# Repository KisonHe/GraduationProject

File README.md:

# ESP32 & RoboMaster motors
水毕设，3508+ESP_Dash，ESP32控制

## LVGL Note
注意检查style的生命周期，要与被赋予style的对象共存亡

```bash
node ./node_modules/lv_font_conv/lv_font_conv.js --font ~/Downloads/NotoSansMonoCJKsc-Regular.otf --symbol "123456abcdef我是中国人" --lcd --size 16 --bpp 4 --format bin -o data/customfont.bin
./node_modules/lv_img_conv/lv_img_conv.js ~/Downloads/gyro-200.png -f -c CF_TRUE_COLOR_ALPHA -t bin --binary-format 565 -o gyro.bin
```

获取Fonts `https://github.com/googlefonts/noto-cjk`

[Download](https://github.com/googlefonts/noto-cjk/raw/main/Sans/Mono/NotoSansMonoCJKsc-Regular.otf)

有空的时候记得修改 `https://github.com/KisonHe/TFT_eSPI_Assi` ，改成支持lv_font_conv

Get Offline Tool
```bash
npm i lv_font_conv
npm i lv_img_conv
```

## ESP32 Note
根据 https://github.com/espressif/arduino-esp32/issues/3079#issuecomment-520161166 
nnd,又要改，直接来吧！

## ESP32 - FreeRTOS
在Commit 754485b中，会出现manager或can read太久没有被执行的问题。TODO:目前没有完全理清楚，初步认定是TaskSkip导致的问题
https://docs.espressif.com/projects/esp-idf/en/v4.3.2/esp32/api-guides/freertos-smp.html#round-robin-scheduling

有趣的现象，如果把lvgl的优先级从2改到22,反而不会出现电机疯掉问题了。初步认为wifi task，isr等以及一大堆task彻底抢占了core0,使得剩下的都在core1上，使得taskskip不再出现

一定要搞清楚！目前为了先弄毕业设计先都pin to core 1

排除以上问题，原因是can的接收频率不稳定，如果can rx是tskNO_AFFINITY则会出现接收频率降低问题。注意官方V4的example
```
xTaskCreatePinnedToCore(twai_receive_task, "TWAI_rx", 4096, NULL, RX_TASK_PRIO, NULL, tskNO_AFFINITY);
```
其中RX_TASK_PRIO为9,需要搞清楚为什么

目前在canrx处于tskNO_AFFINITY情况下，即使将lvgl task降到0也会导致canrx频率下降，急需弄清楚

似乎是因为偷懒带来的惨痛教训，从网上抄的CAN初始化没有仔细看，换成CAN_MODE_NORMAL后似乎没问题了。那么，nnd,为什么从2改到22,反而不会出现电机疯掉问题了？

Nope, is it caused by mqtt? Too late now debug tomorrow. Comment out MQTT see if problem still there. If caused by mqtt consider use https://docs.espressif.com/projects/esp-idf/en/latest/esp32/api-reference/protocols/mqtt.html

大概是WiFi Task在环境太糟糕的时候。。。大概会block太久？没验证，查看丢包现象观察猜测

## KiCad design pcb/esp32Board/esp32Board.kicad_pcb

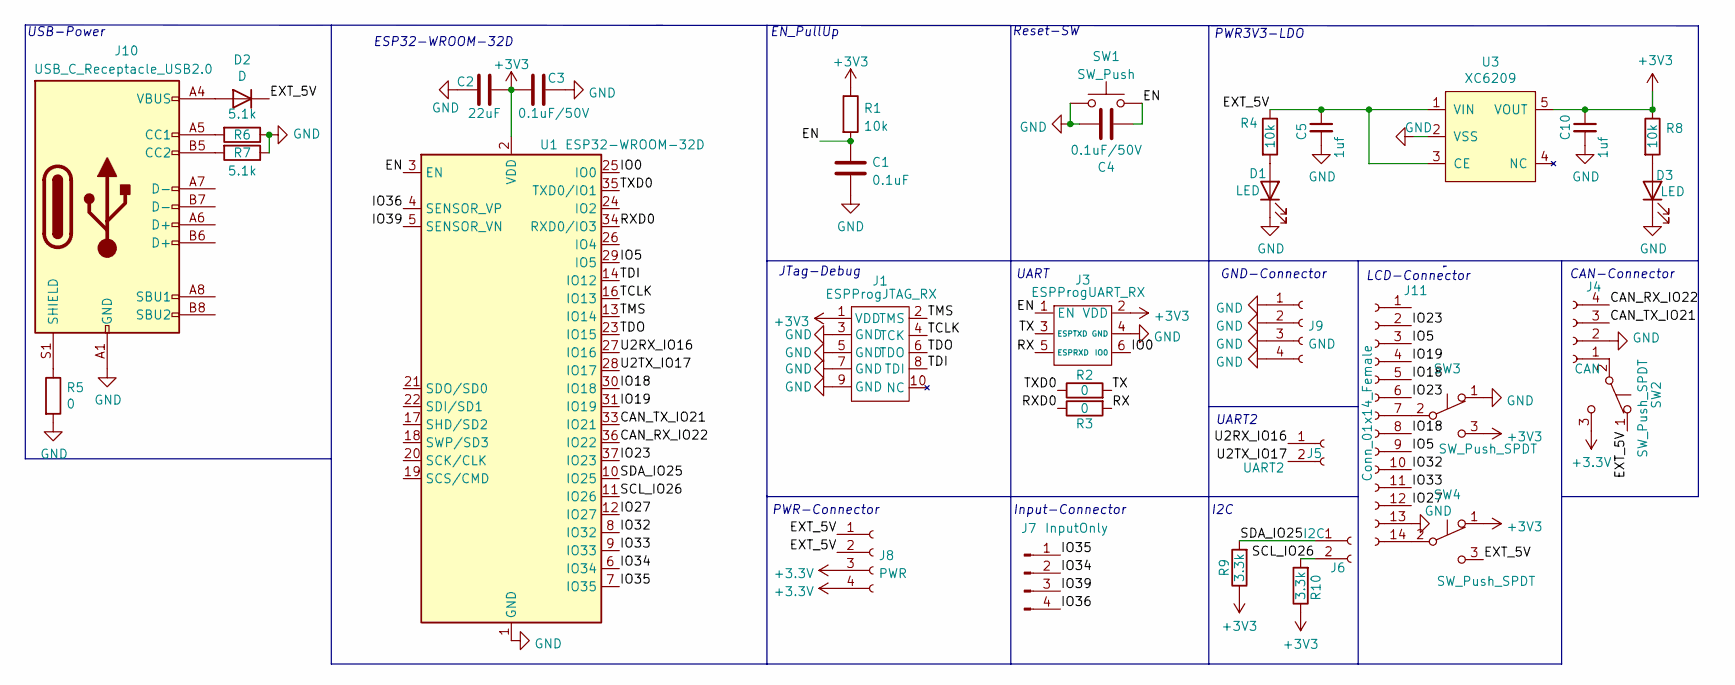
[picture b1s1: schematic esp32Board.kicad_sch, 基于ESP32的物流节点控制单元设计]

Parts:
C1: 0.1uF; C_0603_1608Metric; LCSC C1591
C2: 22uF; C_0603_1608Metric
C3, C4: 0.1uF/50V; C_0603_1608Metric
C5, C10: 1uf; C_0603_1608Metric
D1, D3: LED; LED_0603_1608Metric; LCSC C181863
D2: D; C8678; LCSC C8678
J1: ESPProgJTAG_RX; IDC_1.27mm_10P
J3: ESPProgUART_RX; IDC_1.27mm_6P
J4: CAN; PinHeader_1x04_P2.54mm_Vertical
J5: UART2; PinHeader_1x02_P2.54mm_Vertical
J6: I2C; PinHeader_1x02_P2.54mm_Vertical
J7: InputOnly; PinHeader_1x04_P2.54mm_Vertical
J8: PWR; PinHeader_1x04_P2.54mm_Vertical
J9: GND; PinHeader_1x04_P2.54mm_Vertical
J10: USB_C_Receptacle_USB2.0; USB_C_Receptacle_HRO_TYPE-C-31-M-12; LCSC C165948
J11: Conn_01x14_Female; PinHeader_1x14_P2.54mm_Vertical
R1, R4, R8: 10k; R_0603_1608Metric
R2, R3, R5: 0; R_0603_1608Metric; LCSC C429617
R6, R7: 5.1k; R_0603_1608Metric; LCSC C325524
R9, R10: 3.3k; R_0603_1608Metric; LCSC C429617
SW1: SW_Push; BTN-TS342A4P-WZ-C557592; LCSC C557592
SW2, SW3, SW4: SW_Push_SPDT; 0603JumperP3
U1: ESP32-WROOM-32D; ESP32-WROOM-32
U3: XC6209; SOT-23-5

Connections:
/CAN_RX_IO22: J4.4, U1.36 (IO22)
/CAN_TX_IO21: J4.3, U1.33 (IO21)
/EN: C1.1, C4.1, J3.1 (EN), R1.2, SW1.2, U1.3 (EN)
/EXT_5V: C5.1, D2.1 (K), J8.1, J8.2, R4.1, SW2.1 (A), SW4.3 (C), U3.1 (VIN), U3.3 (CE)
/IO0: J3.6 (IO0), U1.25 (IO0)
/IO5: J11.3, J11.9, U1.29 (IO5)
/IO18: J11.5, J11.8, U1.30 (IO18)
/IO19: J11.4, U1.31 (IO19)
/IO23: J11.2, J11.6, U1.37 (IO23)
/IO27: J11.12, U1.12 (IO27)
/IO32: J11.10, U1.8 (IO32)
/IO33: J11.11, U1.9 (IO33)
/IO34: J7.2, U1.6 (IO34)
/IO35: J7.1, U1.7 (IO35)
/IO36: J7.4, U1.4 (SENSOR_VP)
/IO39: J7.3, U1.5 (SENSOR_VN)
/RX: J3.5 (ESPRXD), R3.2
/RXD0: R3.1, U1.34 (RXD0/IO3)
/SCL_IO26: J6.2, R10.2, U1.11 (IO26)
/SDA_IO25: J6.1, R9.2, U1.10 (IO25)
/TCLK: J1.4 (TCK), U1.16 (IO13)
/TDI: J1.8 (TDI), U1.14 (IO12)
/TDO: J1.6 (TDO), U1.23 (IO15)
/TMS: J1.2 (TMS), U1.13 (IO14)
/TX: J3.3 (ESPTXD), R2.2
/TXD0: R2.1, U1.35 (TXD0/IO1)
/U2RX_IO16: J5.1, U1.27 (IO16)
/U2TX_IO17: J5.2, U1.28 (IO17)
GND: C1.2, C2.1, C3.2, C4.2, C5.2, C10.2, D1.1 (K), D3.1 (K), J1.3 (GND), J1.5 (GND), J1.7 (GND), J1.9 (GND), J3.4 (GND), J4.2, J9.1, J9.2, J9.3, J9.4, J10.A1 (GND), J10.A12 (GND), J10.B1 (GND), J10.B12 (GND), J11.13, R5.2, R6.1, R7.1, SW1.1, SW3.1 (A), U1.1 (GND), U1.15 (GND), U1.38 (GND), U1.39 (GND), U3.2 (VSS)
unnamed: D1.2 (A), R4.2
unnamed: D2.2 (A), J10.A4 (VBUS), J10.A9 (VBUS), J10.B4 (VBUS), J10.B9 (VBUS)
unnamed: D3.2 (A), R8.2
unnamed: J4.1, SW2.2 (B)
unnamed: J10.A5 (CC1), R6.2
unnamed: J10.B5 (CC2), R7.2
unnamed: J10.S1 (SHIELD), R5.1
unnamed: J11.7, SW3.2 (B)
unnamed: J11.14, SW4.2 (B)

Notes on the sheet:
ESP32-WROOM-32D
Input-Connector
LCD-Connector
PWR3V3-LDO
CAN-Connector
USB-Power
EN_PullUp
UART
I2C
GND-Connector
JTag-Debug
Reset-SW
UART2
PWR-Connector

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
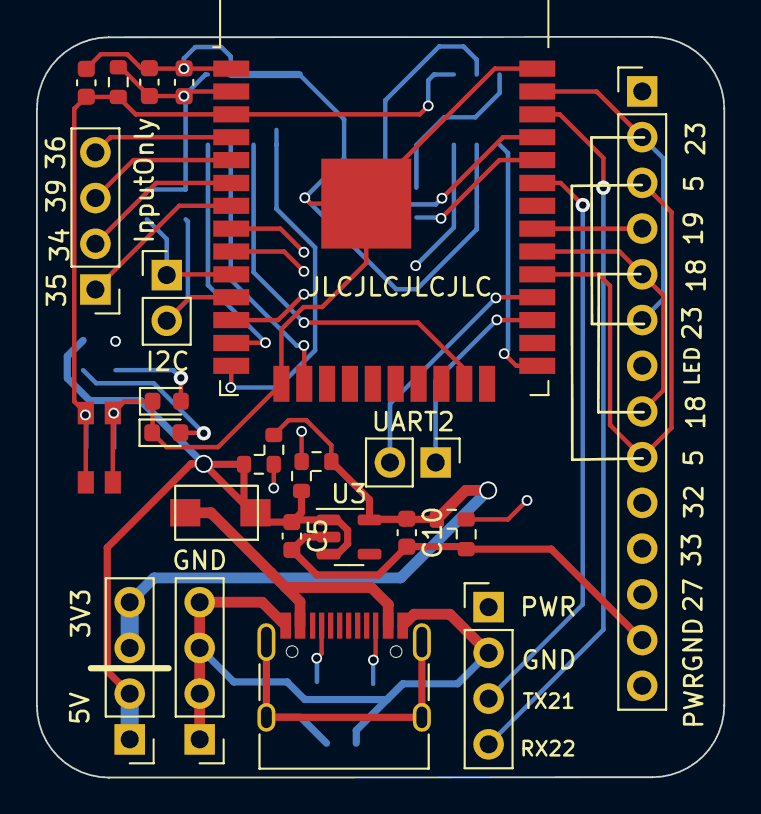
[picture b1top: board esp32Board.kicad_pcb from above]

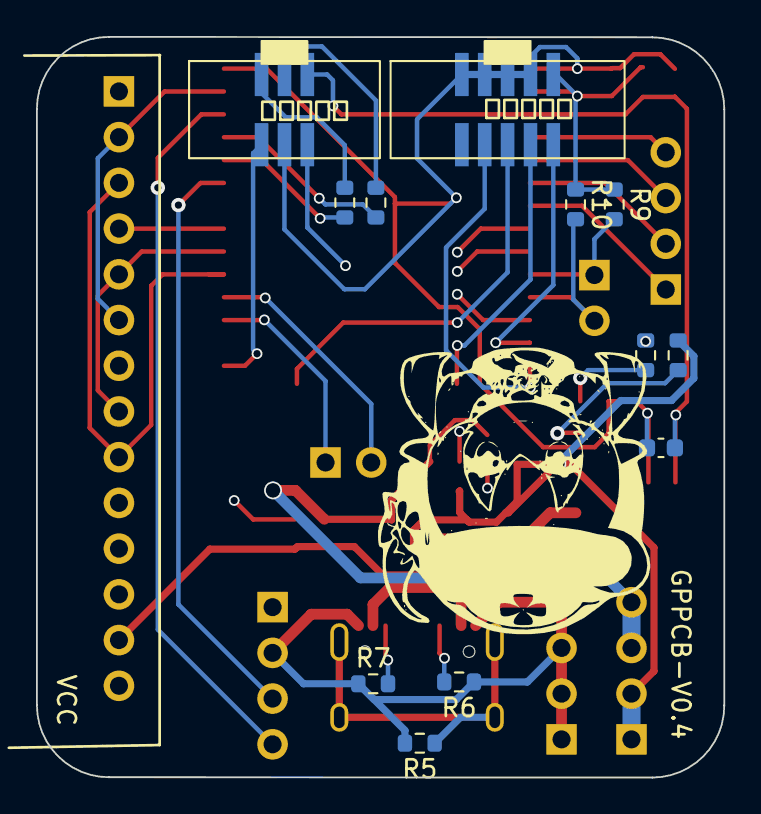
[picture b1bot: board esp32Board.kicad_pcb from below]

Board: 4 copper layers, 38.2 x 41.1 mm, 35 parts (12 on the bottom side), 39 nets.

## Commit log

2022-03-17 Init
2022-03-19 PIDCardSet V1
2022-03-19 Fake Cards
    Make some fake cards so teachers during mid-term check would consider we did a lot of things
2022-03-20 PCB-V0
2022-03-22 PCB Update
2022-03-22 esp log with color
2022-03-22 can motors
2022-03-22 update log
2022-03-23 Pos & Spd control working
2022-03-23 Working With ESP-Dash Now
2022-03-23 README
2022-03-26 Fix PCB Error
2022-03-26 PID区间I积分
2022-03-26 使用新的PCB
2022-03-27 Add partition
2022-03-27 mqtt hb with real data
2022-03-27 更新描述
2022-03-27 modify esp-dash source code
    Because the button is on top of card button,
    preventing people from pressing the card button
2022-03-27 Update ini
    esp-dash is using ArduinoJson already
2022-03-28 PCB V0.2
2022-03-28 MQTT Control
2022-03-28 Bug Fix PID hang
2022-03-29 制作代码垃圾
2022-04-01 Add LVGL Example
2022-04-01 LVGL Font Test
2022-04-01 bin font test
2022-04-02 Arrange Code
2022-04-02 Layout Update
2022-04-02 Add ZeroPosition Support
    Not Tested on Machine yet
2022-04-06 Mutex LVGL
2022-04-06 Imporve GUI Task
2022-04-08 Add motor tab label
2022-04-10 Update label
2022-04-11 Improve Speed
2022-04-12 Fix Touch Bug
2022-04-12 Improve WiFi
2022-04-12 Add FrameWork
2022-04-12 Put ESP-Dash's web into spiffs
2022-04-12 Fix rpmMeter SCROLLABLE bug
2022-04-13 Use XC6209 instead of trash XC6206
2022-04-13 BugFix
2022-04-13 Lower Flash Speed
    Flash Speed at 80M have a significant chance getting
    IllegalInstruction Error. Before moving to XC6209,
    lower the speed of flash instead
2022-04-13 Add some useless info and imgs
2022-04-14 Fix I2C Pull Up
    https://github.com/espressif/arduino-esp32/issues/3424 Damn why not design it strong enough so bad
2022-04-14 Switch to more stable aliyun mqtt broker
2022-04-17 Add spd slider
2022-04-18 Update sch with blocks
2022-04-18 Update control view
2022-04-18 Fix CAN Bus Bug
2022-04-18 Update PCB
2022-04-18 Stop Develop Fancy mqtt side
2022-04-20 Back to Full Flash Speed
2022-04-23 Add Calib button
2022-04-23 Improve Calib
2022-04-23 Bug Fix
2022-04-28 Add poor version mqtt controller
2022-04-28 Mqtt controller
2022-04-29 Fix CAN lose frame problem
2022-04-29 Fix Stupid Bug
2022-05-11 改成竖的，论文好看
